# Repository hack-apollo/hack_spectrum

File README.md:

Hack Labs Audio Spectrum ：https://www.youtube.com/watch?v=lrZFiLHbFRo&lc=Ugw5ZR2V5kvy2mBF6H14AaABAg                                                                                
Author: HACK实验室                                                                                     
YouTube ID: HACK实验室, welcome to subscribe https://www.youtube.com/channel/UCxFY1FcIYK9d7riTvIh6eiA                                                         
Hack Audio Spectrum is a free download and may be used, modified, evaluated and
distributed without charge provided the user adheres to version three of the GNU
General Public License (GPL) and does not remove the copyright notice or this
text.  The GPL V3 text is available on the gnu.org web site
作者：HACK实验室                                                                                        
B站ID：HACK实验室  欢迎订阅 https://space.bilibili.com/395145107                                                                            
微信公众号：HACK实验室，开源资料唯一发布点，定期分享开源硬件以及有价值的技术文章，欢迎关注.

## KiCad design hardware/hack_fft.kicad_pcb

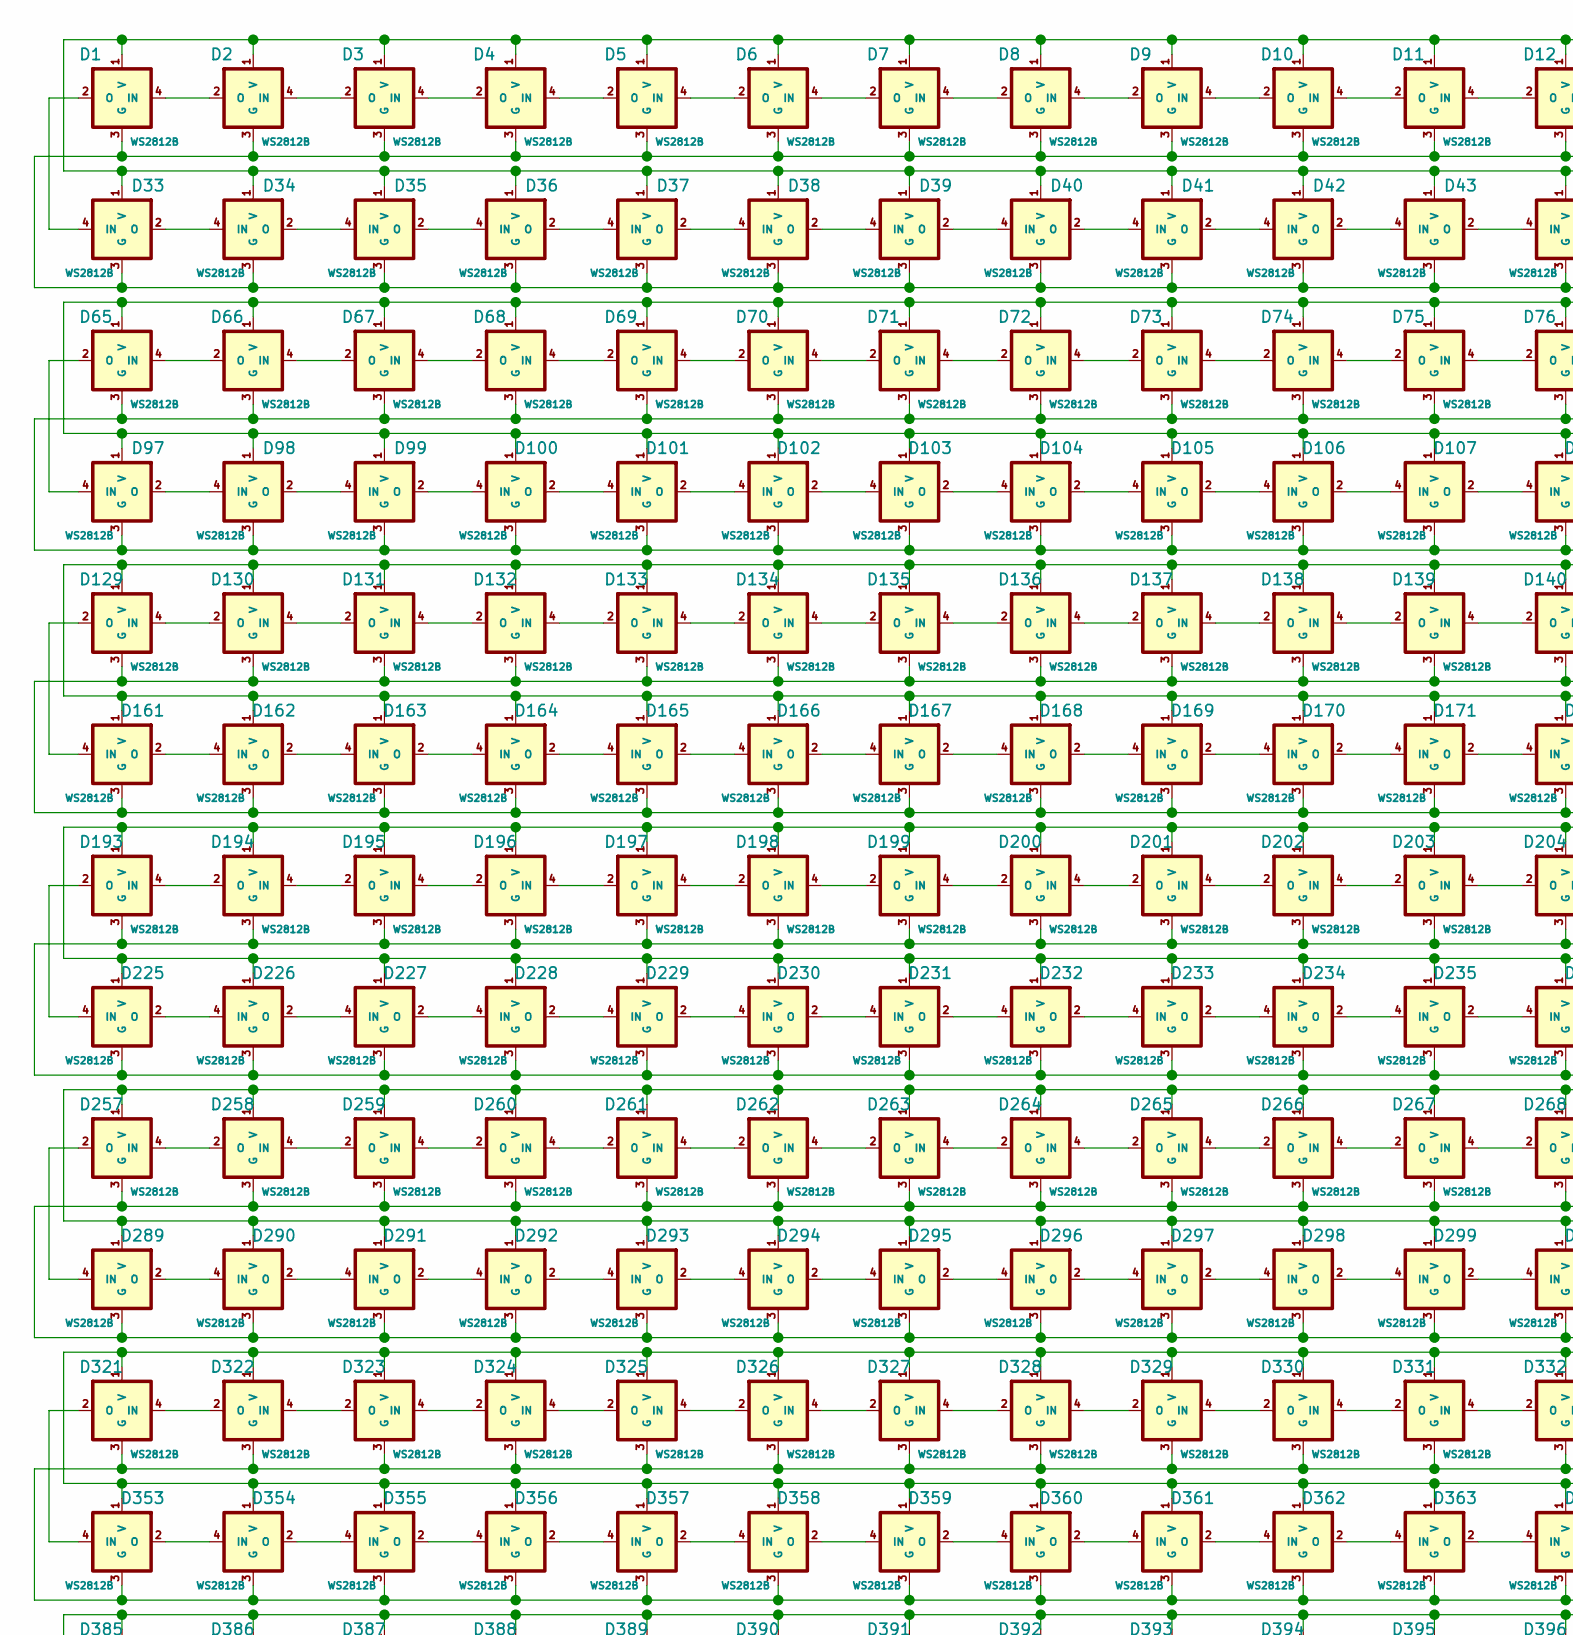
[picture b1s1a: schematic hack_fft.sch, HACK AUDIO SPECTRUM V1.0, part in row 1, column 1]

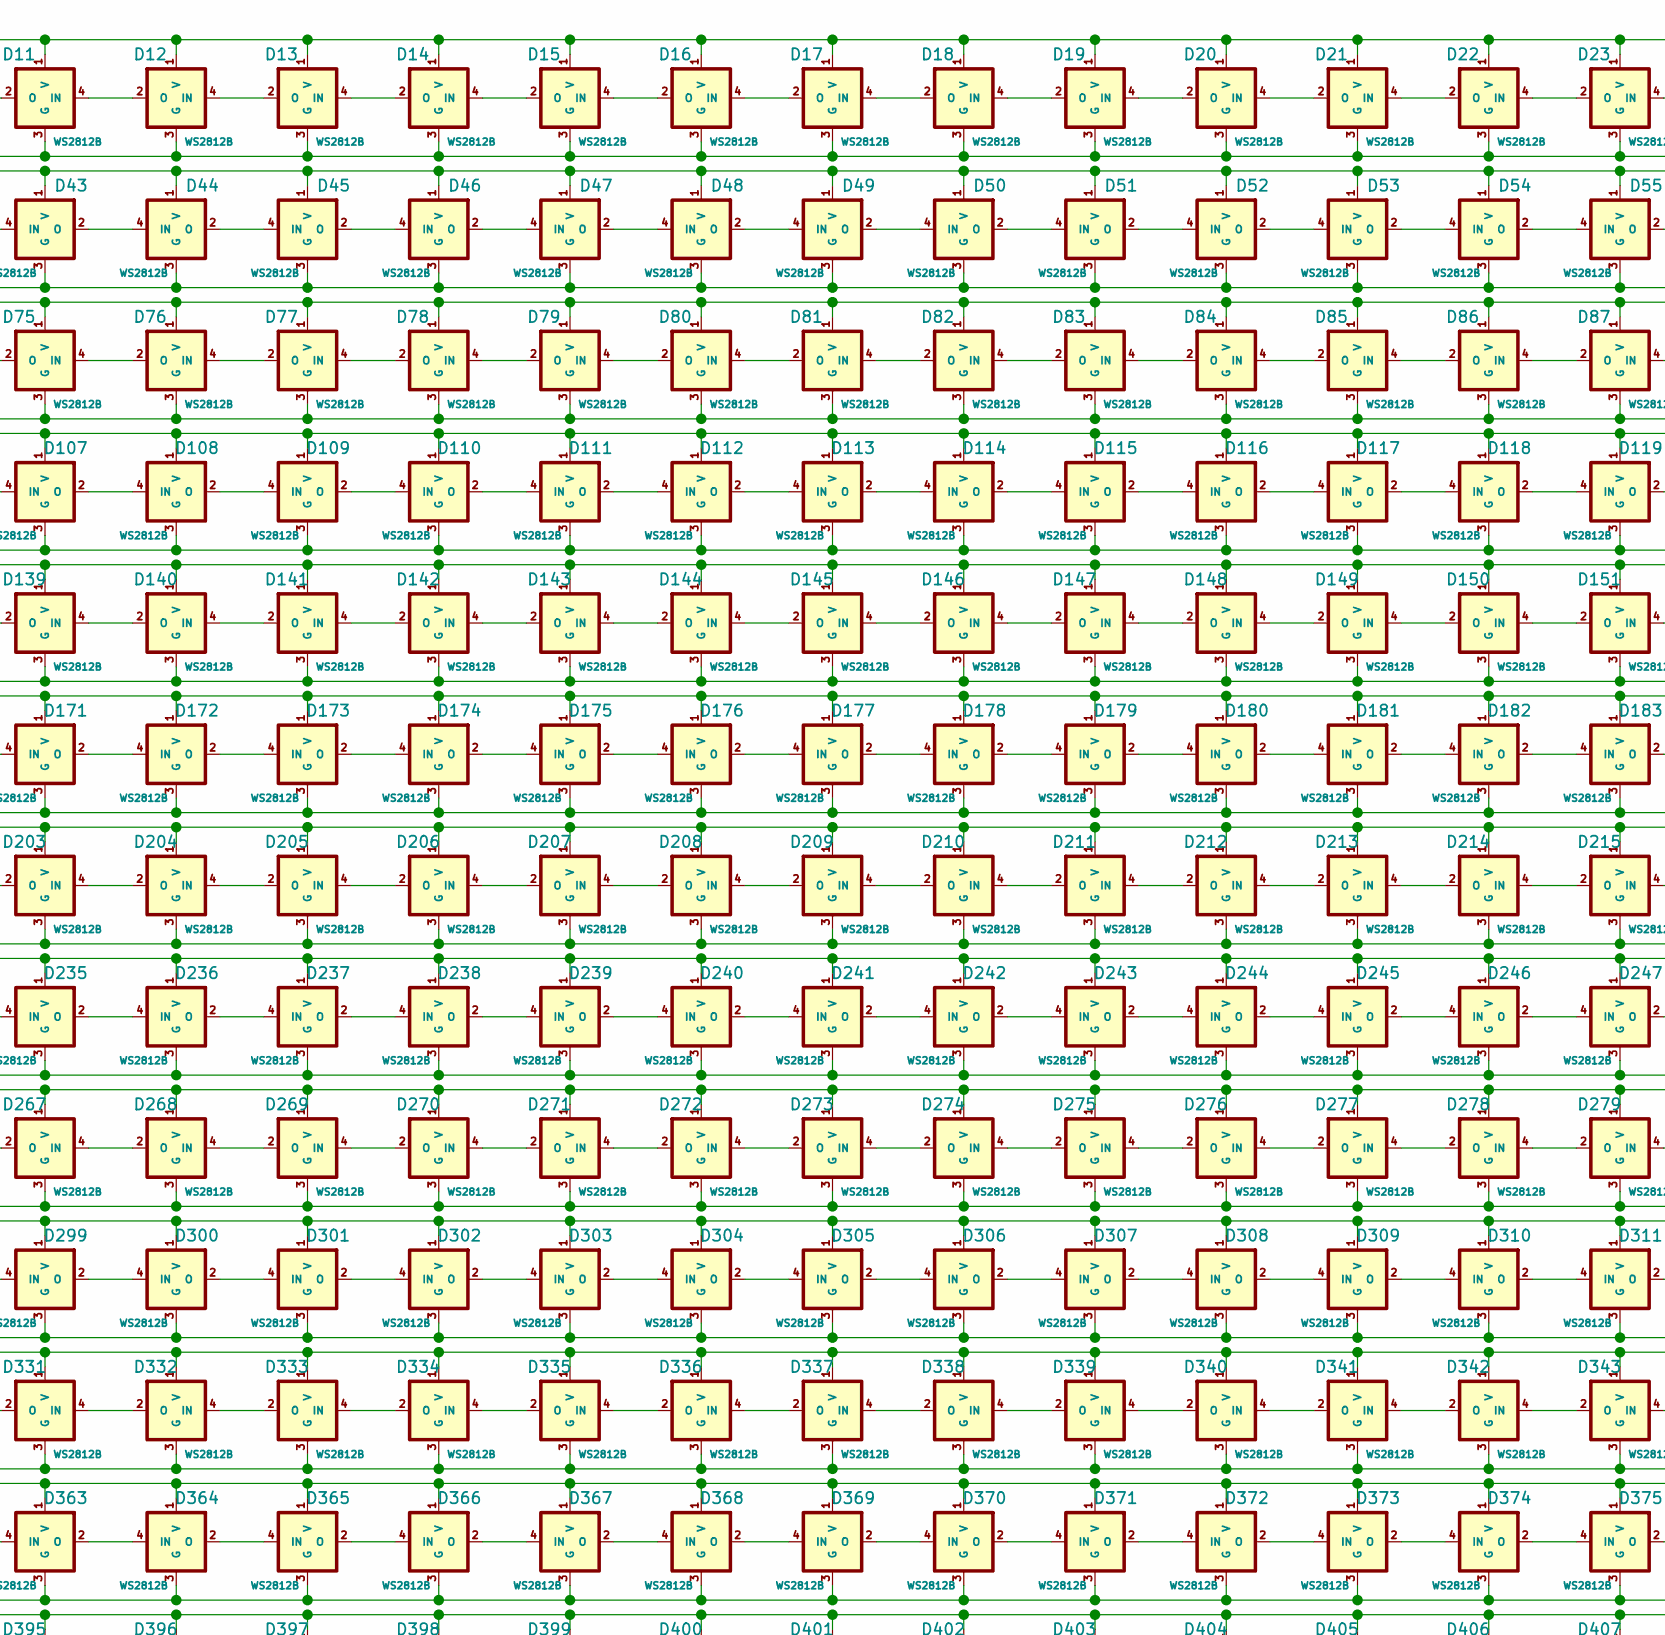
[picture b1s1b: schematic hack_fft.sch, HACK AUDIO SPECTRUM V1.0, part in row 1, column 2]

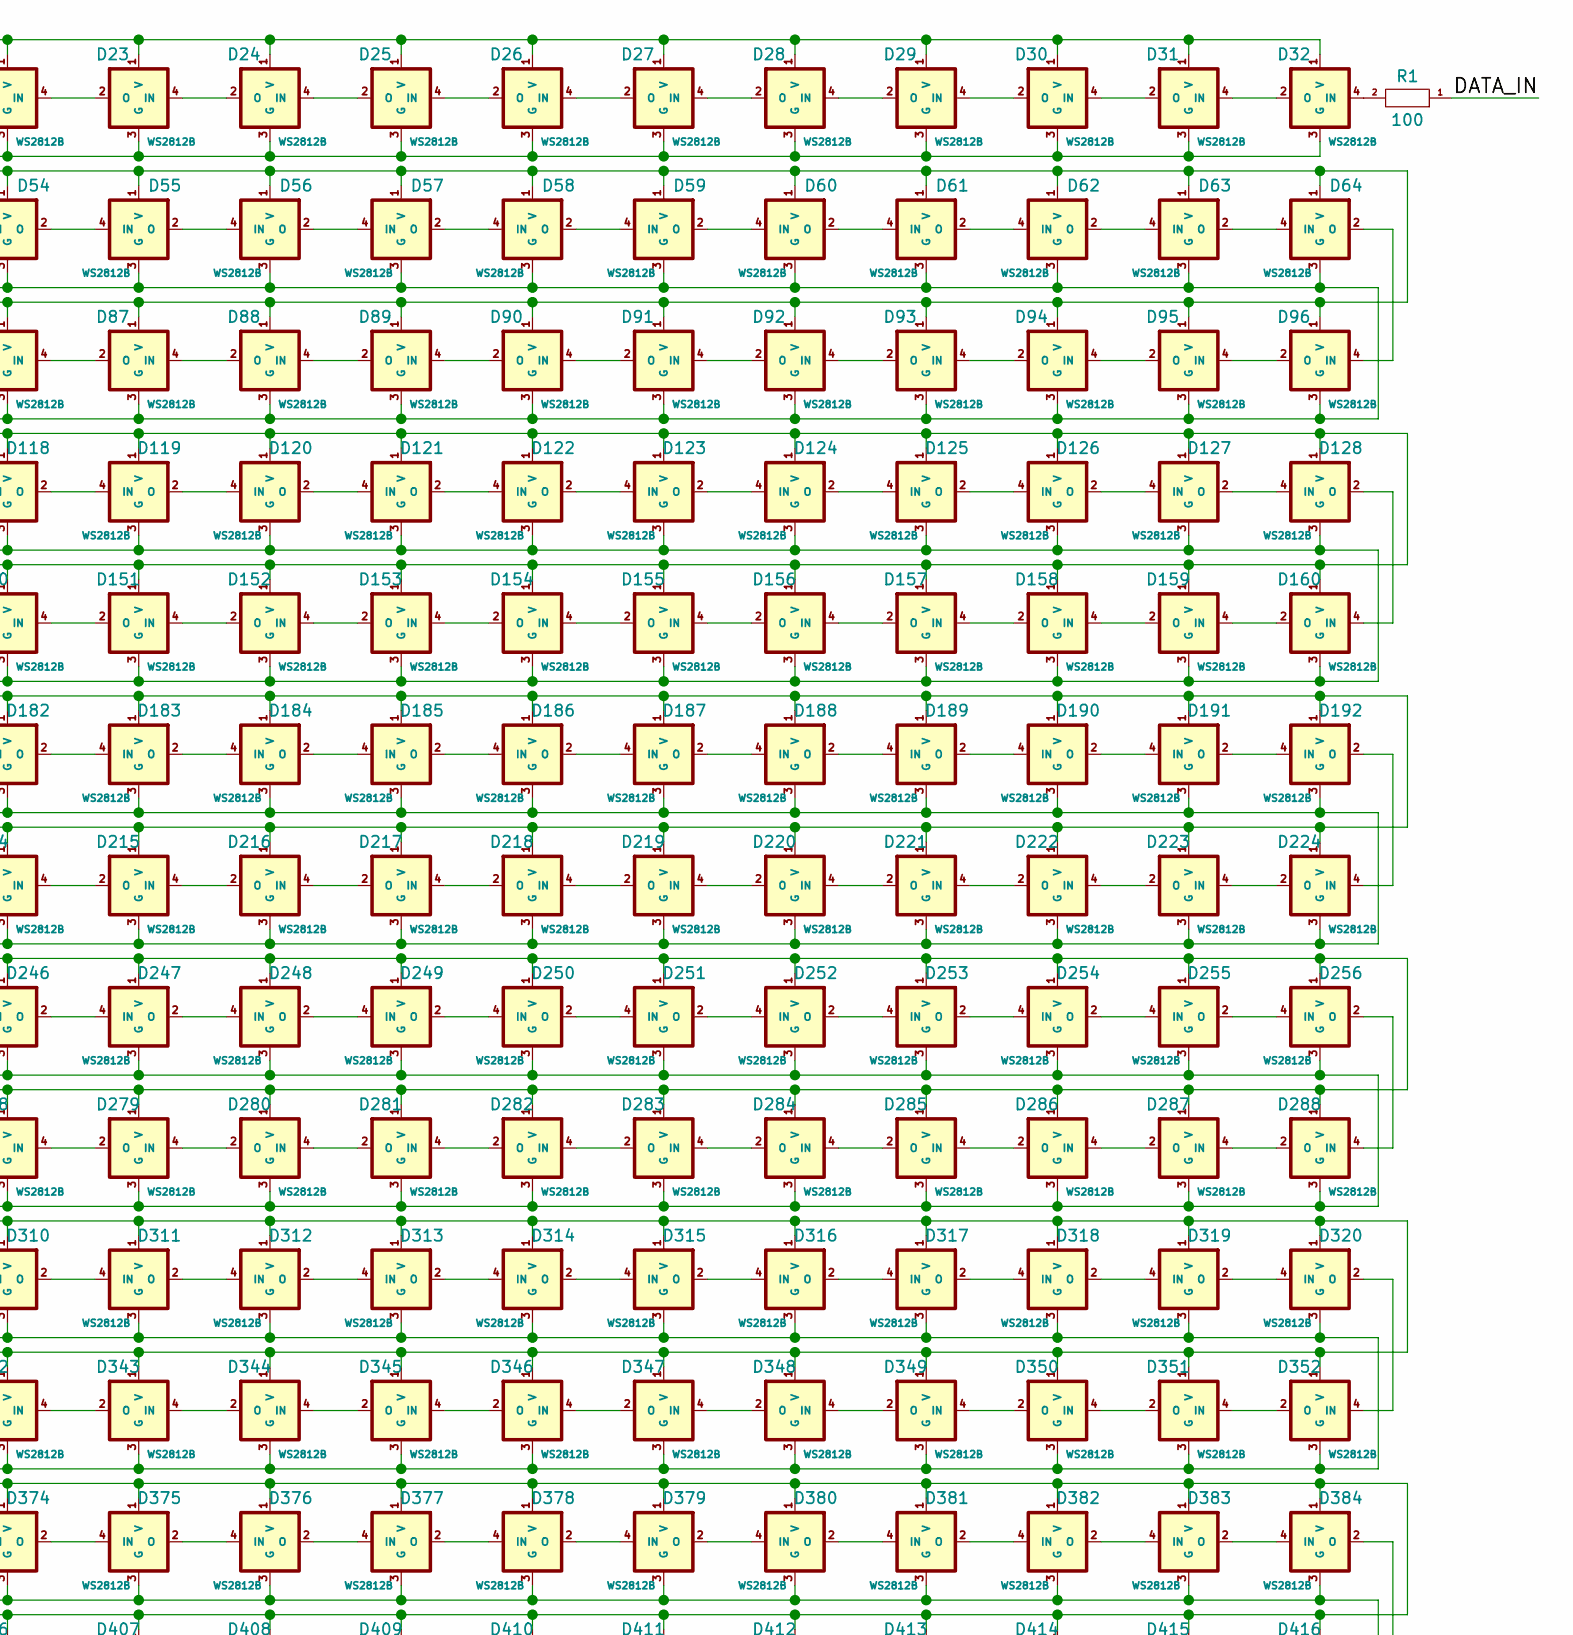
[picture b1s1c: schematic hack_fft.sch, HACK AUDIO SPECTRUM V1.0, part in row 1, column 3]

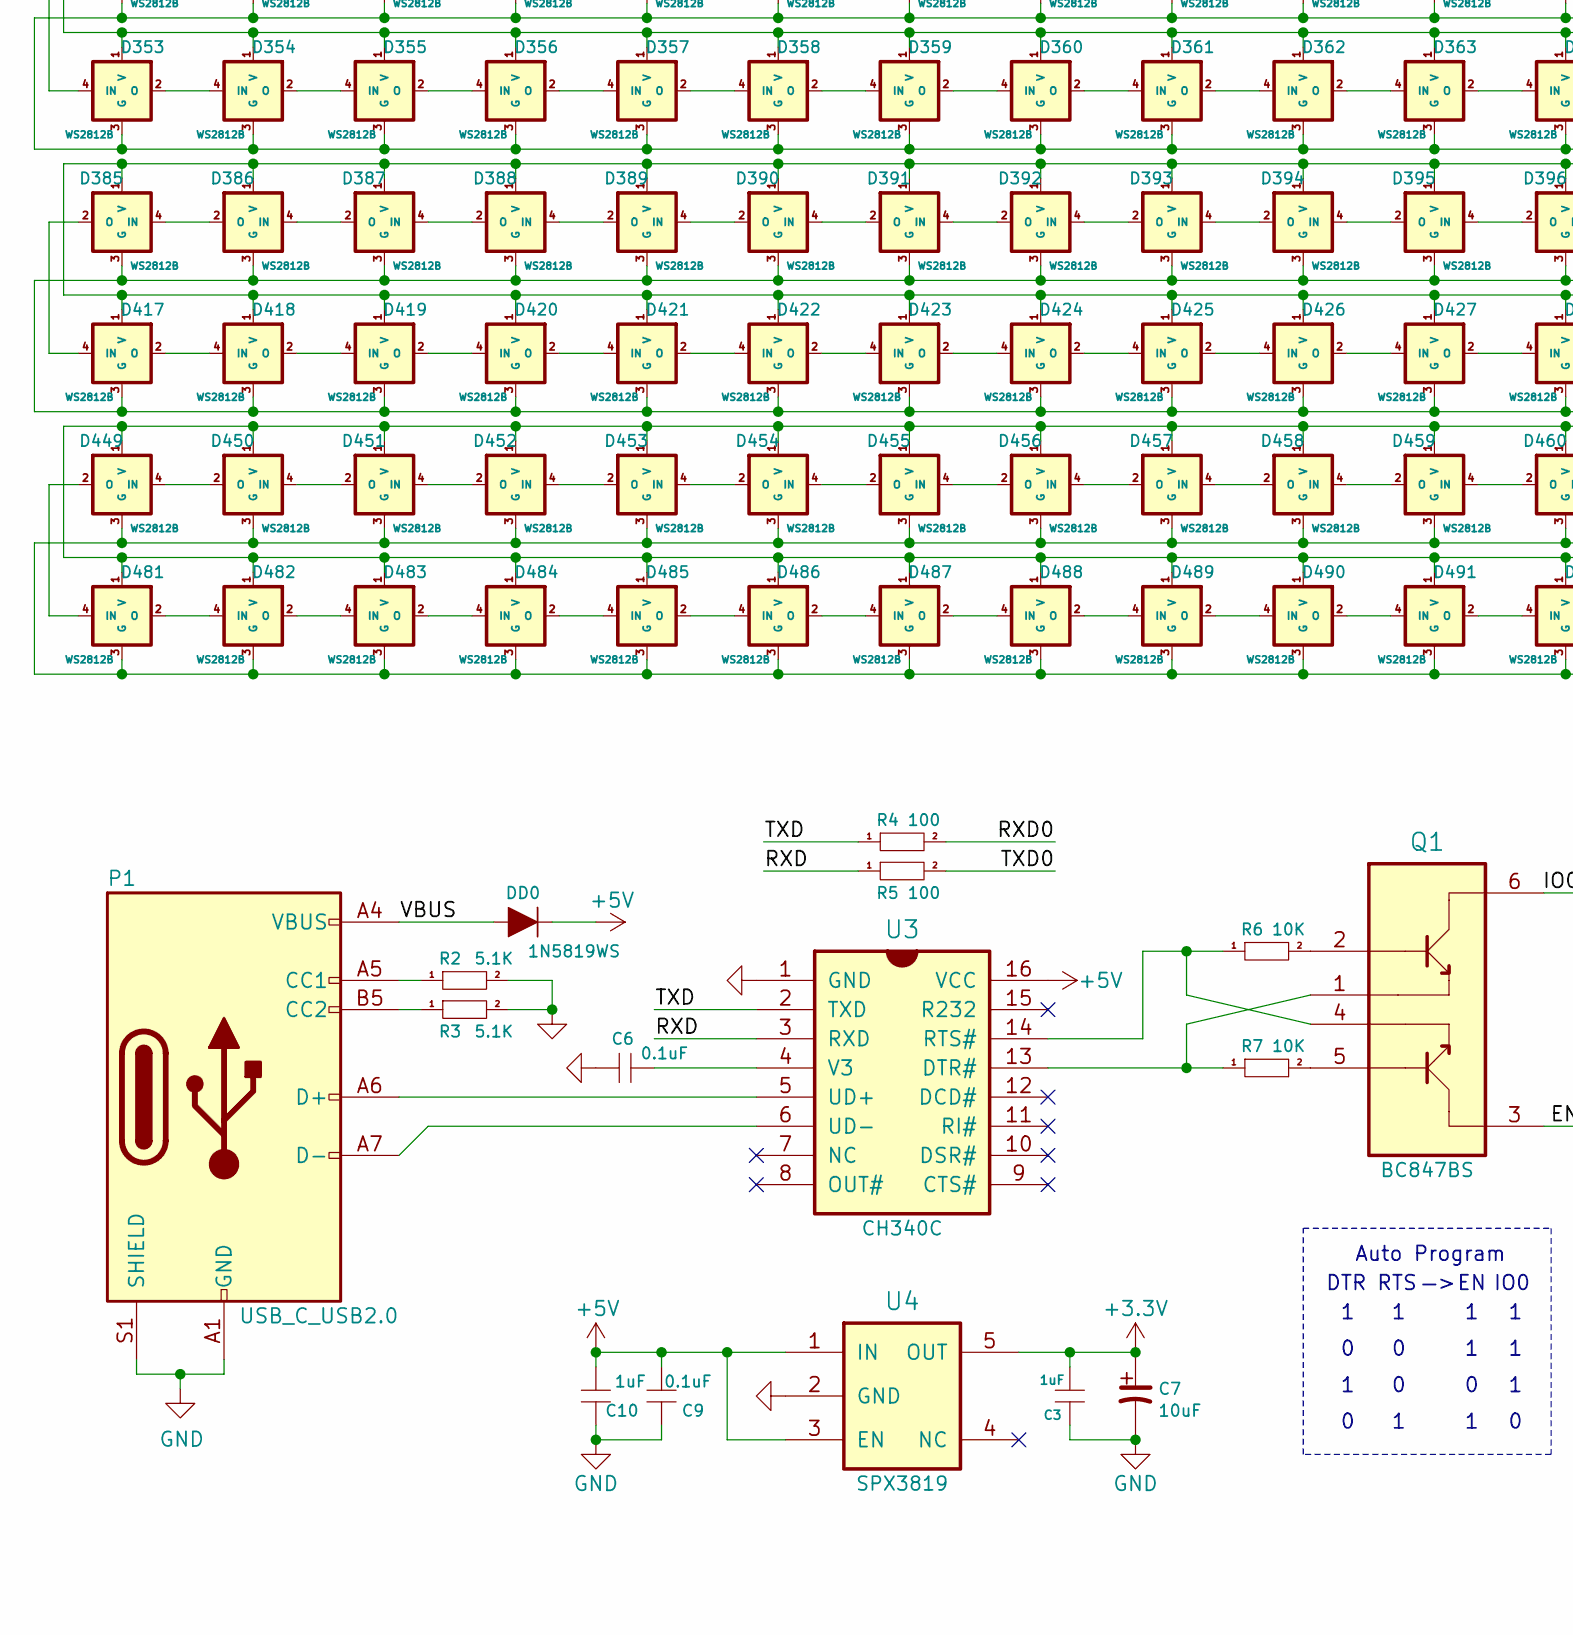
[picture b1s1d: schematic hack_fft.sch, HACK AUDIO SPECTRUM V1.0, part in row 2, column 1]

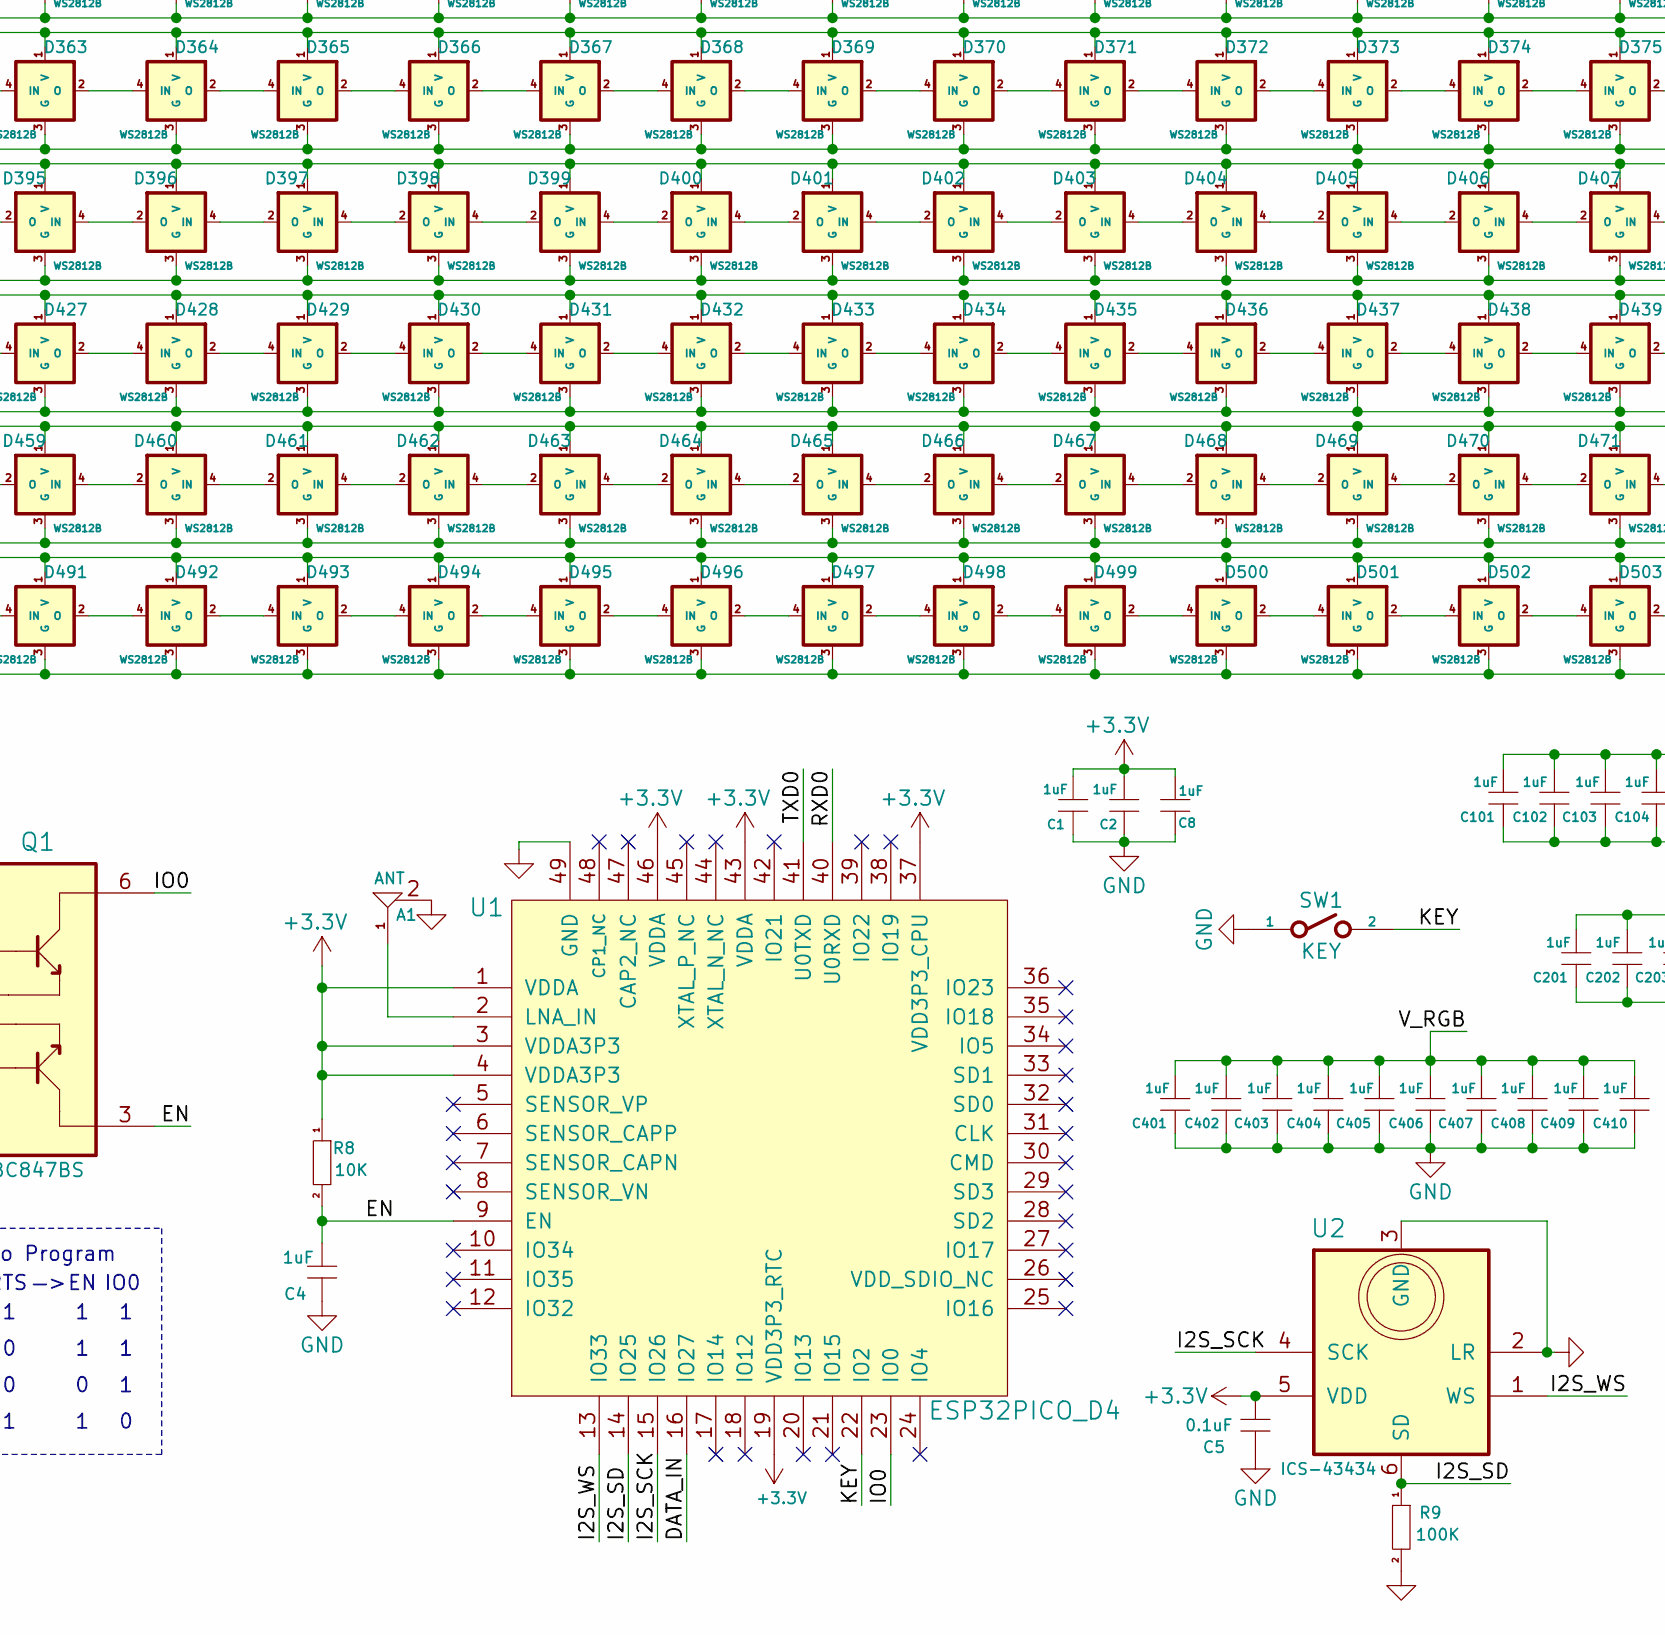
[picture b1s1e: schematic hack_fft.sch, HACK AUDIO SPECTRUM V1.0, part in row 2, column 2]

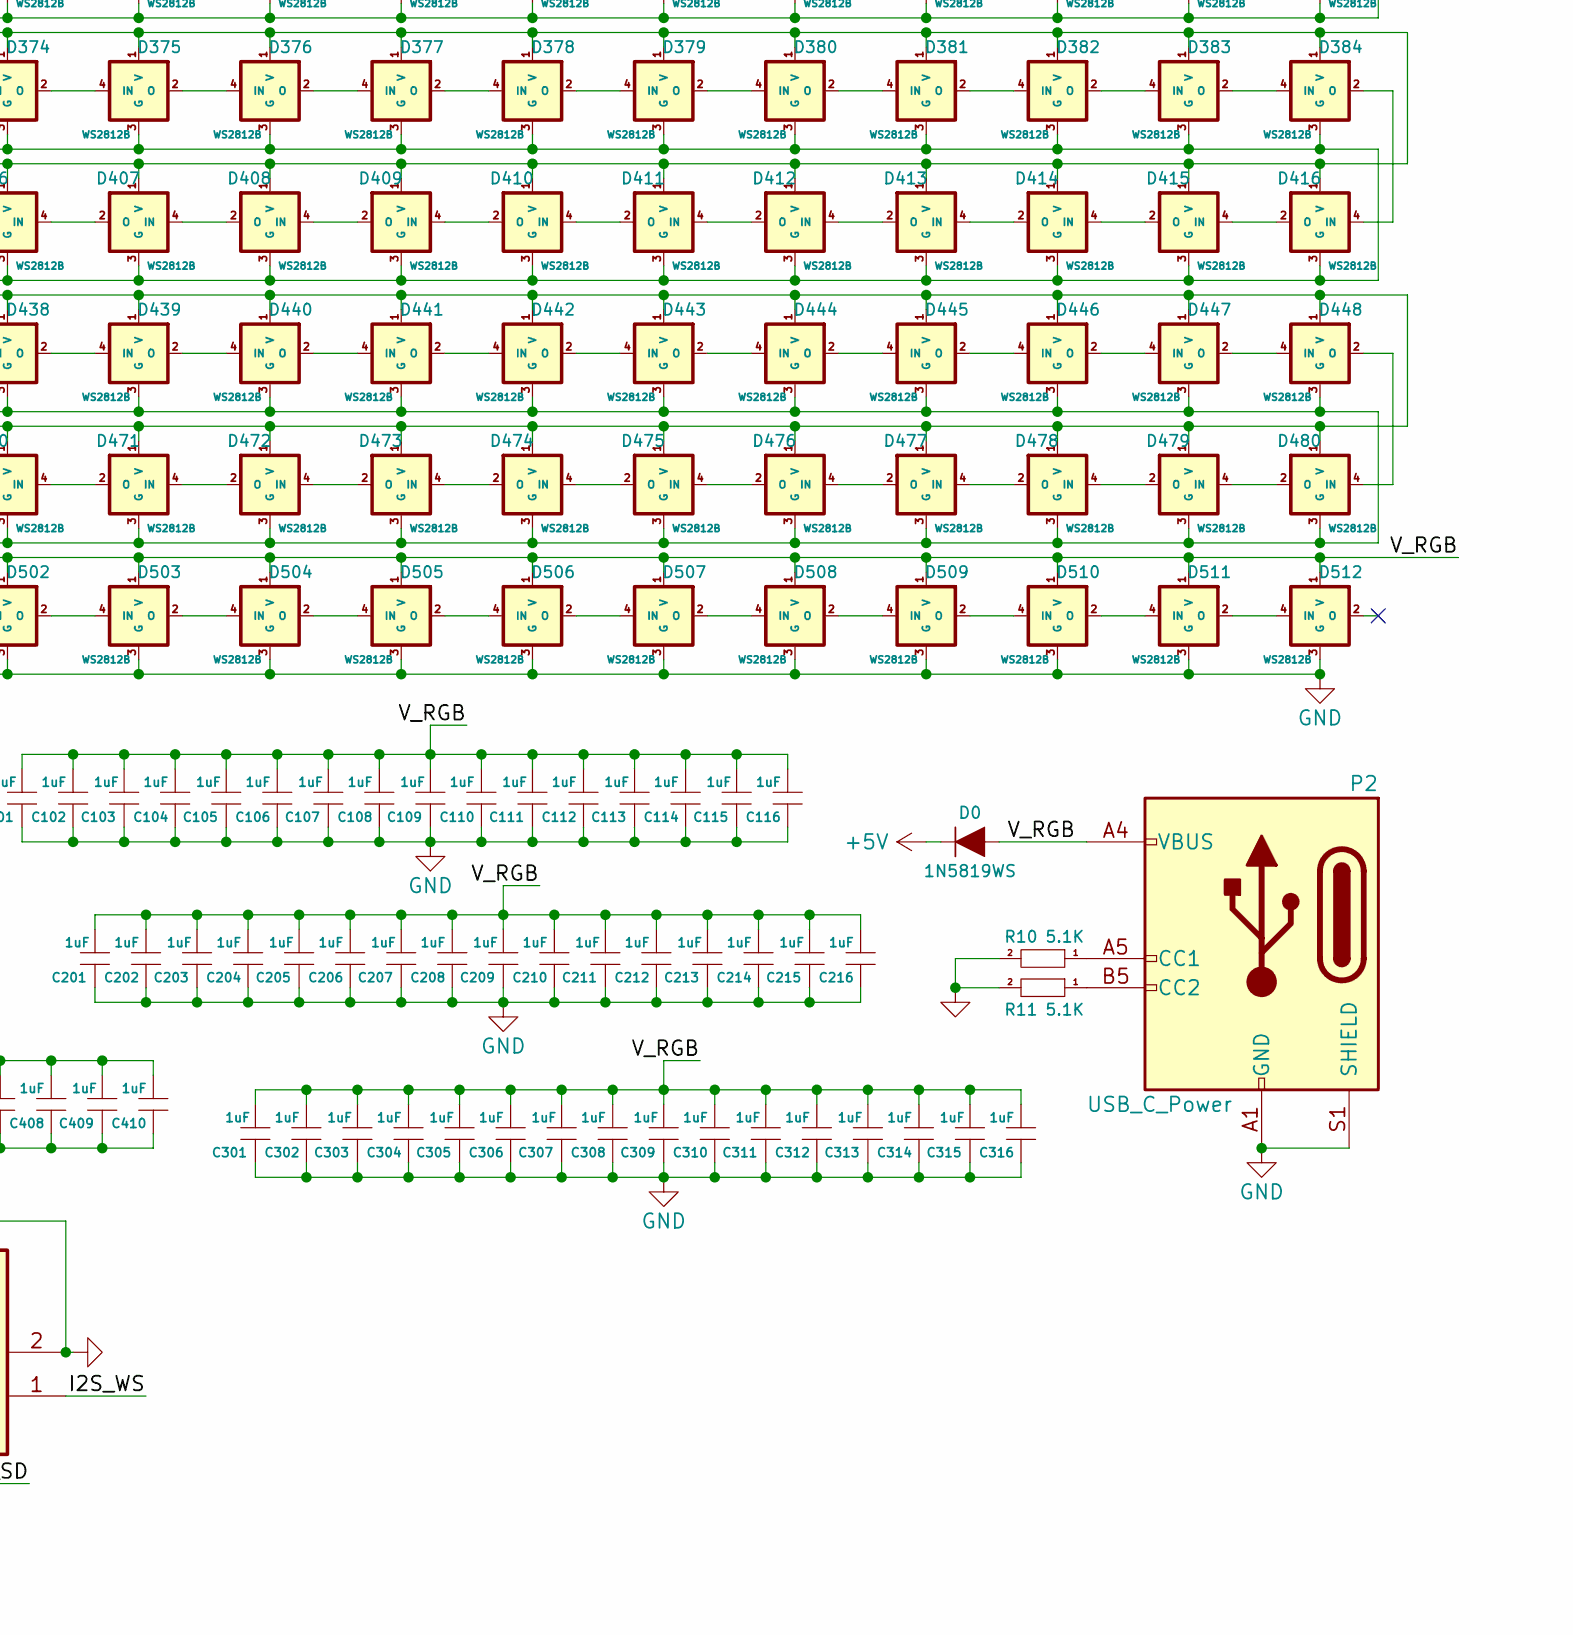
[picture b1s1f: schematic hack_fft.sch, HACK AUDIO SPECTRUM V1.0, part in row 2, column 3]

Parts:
A1: ANT; ProAnt_PRO-OB-440
C1, C2, C3, C4, C8, C10, C101, C102, C103, C104, C105, C106, C107, C108, C109, C110, C111, C112, C113, C114, C115, C116, C201, C202, C203, C204, C205, C206, C207, C208, C209, C210, C211, C212, C213, C214, C215, C216, C301, C302, C303, C304, C305, C306, C307, C308, C309, C310, C311, C312, C313, C314, C315, C316, C401, C402, C403, C404, C405, C406, C407, C408, C409, C410: 1uF; 0603_C
C5, C6, C9: 0.1uF; 0603_C
C7: 10uF; TantalC_SizeT_3528
D0: 1N5819WS; F_1206
D1, D2, D3, D4, D5, D6, D7, D8, D9, D10, D11, D12, D13, D14, D15, D16, D17, D18, D19, D20, D21, D22, D23, D24, D25, D26, D27, D28, D29, D30, D31, D32, D33, D34, D35, D36, D37, D38, D39, D40, D41, D42, D43, D44, D45, D46, D47, D48, D49, D50, D51, D52, D53, D54, D55, D56, D57, D58, D59, D60, D61, D62, D63, D64, D65, D66, D67, D68, D69, D70, D71, D72, D73, D74, D75, D76, D77, D78, D79, D80, D81, D82, D83, D84, D85, D86, D87, D88, D89, D90, D91, D92, D93, D94, D95, D96, D97, D98, D99, D100, D101, D102, D103, D104, D105, D106, D107, D108, D109, D110, D111, D112, D113, D114, D115, D116, D117, D118, D119, D120, D121, D122, D123, D124, D125, D126, D127, D128, D129, D130, D131, D132, D133, D134, D135, D136, D137, D138, D139, D140, D141, D142, D143, D144, D145, D146, D147, D148, D149, D150, D151, D152, D153, D154, D155, D156, D157, D158, D159, D160, D161, D162, D163, D164, D165, D166, D167, D168, D169, D170, D171, D172, D173, D174, D175, D176, D177, D178, D179, D180, D181, D182, D183, D184, D185, D186, D187, D188, D189, D190, D191, D192, D193, D194, D195, D196, D197, D198, D199, D200, D201, D202, D203, D204, D205, D206, D207, D208, D209, D210, D211, D212, D213, D214, D215, D216, D217, D218, D219, D220, D221, D222, D223, D224, D225, D226, D227, D228, D229, D230, D231, D232, D233, D234, D235, D236, D237, D238, D239, D240, D241, D242, D243, D244, D245, D246, D247, D248, D249, D250, D251, D252, D253, D254, D255, D256, D257, D258, D259, D260, D261, D262, D263, D264, D265, D266, D267, D268, D269, D270, D271, D272, D273, D274, D275, D276, D277, D278, D279, D280, D281, D282, D283, D284, D285, D286, D287, D288, D289, D290, D291, D292, D293, D294, D295, D296, D297, D298, D299, D300, D301, D302, D303, D304, D305, D306, D307, D308, D309, D310, D311, D312, D313, D314, D315, D316, D317, D318, D319, D320, D321, D322, D323, D324, D325, D326, D327, D328, D329, D330, D331, D332, D333, D334, D335, D336, D337, D338, D339, D340, D341, D342, D343, D344, D345, D346, D347, D348, D349, D350, D351, D352, D353, D354, D355, D356, D357, D358, D359, D360, D361, D362, D363, D364, D365, D366, D367, D368, D369, D370, D371, D372, D373, D374, D375, D376, D377, D378, D379, D380, D381, D382, D383, D384, D385, D386, D387, D388, D389, D390, D391, D392, D393, D394, D395, D396, D397, D398, D399, D400, D401, D402, D403, D404, D405, D406, D407, D408, D409, D410, D411, D412, D413, D414, D415, D416, D417, D418, D419, D420, D421, D422, D423, D424, D425, D426, D427, D428, D429, D430, D431, D432, D433, D434, D435, D436, D437, D438, D439, D440, D441, D442, D443, D444, D445, D446, D447, D448, D449, D450, D451, D452, D453, D454, D455, D456, D457, D458, D459, D460, D461, D462, D463, D464, D465, D466, D467, D468, D469, D470, D471, D472, D473, D474, D475, D476, D477, D478, D479, D480, D481, D482, D483, D484, D485, D486, D487, D488, D489, D490, D491, D492, D493, D494, D495, D496, D497, D498, D499, D500, D501, D502, D503, D504, D505, D506, D507, D508, D509, D510, D511, D512: WS2812B; LED_WS2812B_3.5x3.5mm
DD0: 1N5819WS; F_1206
P1: USB_C_USB2.0; USB-Type-C-SMD
P2: USB_C_Power; USB-Type-C-Stand
Q1: BC847BS; SOT363
R1, R4, R5: 100; 0603_R
R2, R3, R10, R11: 5.1K; 0603_R
R6, R7, R8: 10K; 0603_R
R9: 100K; 0603_R
SW1: KEY; SWITCH_PUSH_4
U1: ESP32PICO_D4; QFN-48-1EP_7x7mm_P0.5mm_ESP32PICO-D4
U2: ICS-43434
U3: CH340C; SOP-16
U4: SPX3819; SOT23-5

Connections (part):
+3V3: C1.2, C2.2, C3.2, C5.2, C7.1, C8.2, R8.1, U1.1 (VDDA), U1.3 (VDDA3P3), U1.4 (VDDA3P3), U1.19 (VDD3P3_RTC), U1.37 (VDD3P3_CPU), U1.43 (VDDA), U1.46 (VDDA), U2.5 (VDD), U4.5 (OUT)
+5V: C9.2, C10.2, D0.2 (K), DD0.2 (K), U3.16 (VCC), U4.1 (IN), U4.3 (EN)
/DATA_IN: R1.1, U1.16 (IO27)
/EN: C4.2, Q1.3, R8.2, U1.9 (EN)
/I2S_SCK: U1.15 (IO26), U2.4 (SCK)
/I2S_SD: R9.1, U1.14 (IO25), U2.6 (SD)
/I2S_WS: U1.13 (IO33), U2.1 (WS)
/IO0: Q1.6, U1.23 (IO0)
/KEY: SW1.2, U1.22 (IO2)
/RXD: R5.1, U3.3 (RXD)
/RXD0: R4.2, U1.40 (U0RXD)
/TXD: R4.1, U3.2 (TXD)
/TXD0: R5.2, U1.41 (U0TXD)
/VBUS: DD0.1 (A), P1.A4 (VBUS), P1.A9 (VBUS), P1.B4 (VBUS), P1.B9 (VBUS)
/V_RGB: C101.2, C102.2, C103.2, C104.2, C105.2, C106.2, C107.2, C108.2, C109.2, C110.2, C111.2, C112.2, C113.2, C114.2, C115.2, C116.2, C201.2, C202.2, C203.2, C204.2, C205.2, C206.2, C207.2, C208.2, C209.2, C210.2, C211.2, C212.2, C213.2, C214.2, C215.2, C216.2, C301.2, C302.2, C303.2, C304.2, C305.2, C306.2, C307.2, C308.2, C309.2, C310.2, C311.2, C312.2, C313.2, C314.2, C315.2, C316.2, C401.2, C402.2, C403.2, C404.2, C405.2, C406.2, C407.2, C408.2, C409.2, C410.2, D0.1 (A), D1.1 (V), D2.1 (V), D3.1 (V), D4.1 (V), D5.1 (V), D6.1 (V), D7.1 (V), D8.1 (V), D9.1 (V), D10.1 (V), D11.1 (V), D12.1 (V), D13.1 (V), D14.1 (V), D15.1 (V), D16.1 (V), D17.1 (V), D18.1 (V), D19.1 (V), D20.1 (V), D21.1 (V)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; also elsewhere on the board
GND: A1.2, C1.1, C2.1, C3.1, C4.1, C5.1, C6.1, C7.2, C8.1, C9.1, C10.1, C101.1, C102.1, C103.1, C104.1, C105.1, C106.1, C107.1, C108.1, C109.1, C110.1, C111.1, C112.1, C113.1, C114.1, C115.1, C116.1, C201.1, C202.1, C203.1, C204.1, C205.1, C206.1, C207.1, C208.1, C209.1, C210.1, C211.1, C212.1, C213.1, C214.1, C215.1, C216.1, C301.1, C302.1, C303.1, C304.1, C305.1, C306.1, C307.1, C308.1, C309.1, C310.1, C311.1, C312.1, C313.1, C314.1, C315.1, C316.1, C401.1, C402.1, C403.1, C404.1, C405.1, C406.1, C407.1, C408.1, C409.1, C410.1, D1.3 (G), D2.3 (G), D3.3 (G), D4.3 (G), D5.3 (G), D6.3 (G), D7.3 (G), D8.3 (G), D9.3 (G), D10.3 (G), D11.3 (G)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; also elsewhere on the board
unnamed: A1.1, U1.2 (LNA_IN)
unnamed: C6.2, U3.4 (V3)
unnamed: D1.2 (O), D33.4 (IN)
unnamed: D1.4 (IN), D2.2 (O)
unnamed: D2.4 (IN), D3.2 (O)
unnamed: D3.4 (IN), D4.2 (O)
unnamed: D4.4 (IN), D5.2 (O)
unnamed: D5.4 (IN), D6.2 (O)
unnamed: D6.4 (IN), D7.2 (O)
unnamed: D7.4 (IN), D8.2 (O)
unnamed: D8.4 (IN), D9.2 (O)
unnamed: D9.4 (IN), D10.2 (O)
unnamed: D10.4 (IN), D11.2 (O)
unnamed: D11.4 (IN), D12.2 (O)
unnamed: D12.4 (IN), D13.2 (O)
unnamed: D13.4 (IN), D14.2 (O)
unnamed: D14.4 (IN), D15.2 (O)
unnamed: D15.4 (IN), D16.2 (O)
unnamed: D16.4 (IN), D17.2 (O)
unnamed: D17.4 (IN), D18.2 (O)
unnamed: D18.4 (IN), D19.2 (O)
unnamed: D19.4 (IN), D20.2 (O)
unnamed: D20.4 (IN), D21.2 (O)
unnamed: D21.4 (IN), D22.2 (O)
unnamed: D22.4 (IN), D23.2 (O)
unnamed: D23.4 (IN), D24.2 (O)
unnamed: D24.4 (IN), D25.2 (O)
unnamed: D25.4 (IN), D26.2 (O)
unnamed: D26.4 (IN), D27.2 (O)
unnamed: D27.4 (IN), D28.2 (O)
unnamed: D28.4 (IN), D29.2 (O)
unnamed: D29.4 (IN), D30.2 (O)
unnamed: D30.4 (IN), D31.2 (O)
unnamed: D31.4 (IN), D32.2 (O)
unnamed: D32.4 (IN), R1.2
unnamed: D33.2 (O), D34.4 (IN)
unnamed: D34.2 (O), D35.4 (IN)
unnamed: D35.2 (O), D36.4 (IN)
unnamed: D36.2 (O), D37.4 (IN)
unnamed: D37.2 (O), D38.4 (IN)
unnamed: D38.2 (O), D39.4 (IN)
unnamed: D39.2 (O), D40.4 (IN)
unnamed 58: D40.2 (O), D41.4 (IN); also elsewhere on the board
unnamed 59: D41.2 (O), D42.4 (IN); also elsewhere on the board
unnamed: D42.2 (O), D43.4 (IN)
unnamed: D43.2 (O), D44.4 (IN)
unnamed: D44.2 (O), D45.4 (IN)
unnamed: D45.2 (O), D46.4 (IN)
unnamed: D46.2 (O), D47.4 (IN)
unnamed: D47.2 (O), D48.4 (IN)
unnamed: D48.2 (O), D49.4 (IN)
unnamed: D49.2 (O), D50.4 (IN)
unnamed: D50.2 (O), D51.4 (IN)
unnamed: D51.2 (O), D52.4 (IN)
unnamed: D52.2 (O), D53.4 (IN)
unnamed: D53.2 (O), D54.4 (IN)
unnamed: D54.2 (O), D55.4 (IN)
unnamed: D55.2 (O), D56.4 (IN)
unnamed: D56.2 (O), D57.4 (IN)
unnamed: D57.2 (O), D58.4 (IN)
unnamed: D58.2 (O), D59.4 (IN)
unnamed: D59.2 (O), D60.4 (IN)
unnamed: D60.2 (O), D61.4 (IN)
unnamed: D61.2 (O), D62.4 (IN)
unnamed: D62.2 (O), D63.4 (IN)
unnamed: D63.2 (O), D64.4 (IN)
unnamed: D64.2 (O), D96.4 (IN)
unnamed: D65.2 (O), D97.4 (IN)
unnamed: D65.4 (IN), D66.2 (O)
unnamed: D66.4 (IN), D67.2 (O)
unnamed: D67.4 (IN), D68.2 (O)
unnamed: D68.4 (IN), D69.2 (O)
unnamed: D69.4 (IN), D70.2 (O)
unnamed: D70.4 (IN), D71.2 (O)
unnamed: D71.4 (IN), D72.2 (O)
unnamed: D72.4 (IN), D73.2 (O)
unnamed: D73.4 (IN), D74.2 (O)
unnamed: D74.4 (IN), D75.2 (O)
unnamed: D75.4 (IN), D76.2 (O)
unnamed: D76.4 (IN), D77.2 (O)
unnamed: D77.4 (IN), D78.2 (O)
unnamed: D78.4 (IN), D79.2 (O)
unnamed: D79.4 (IN), D80.2 (O)
unnamed: D80.4 (IN), D81.2 (O)
unnamed: D81.4 (IN), D82.2 (O)
unnamed: D82.4 (IN), D83.2 (O)
unnamed: D83.4 (IN), D84.2 (O)
unnamed: D84.4 (IN), D85.2 (O)
unnamed: D85.4 (IN), D86.2 (O)
unnamed: D86.4 (IN), D87.2 (O)
unnamed: D87.4 (IN), D88.2 (O)
unnamed: D88.4 (IN), D89.2 (O)
unnamed: D89.4 (IN), D90.2 (O)
unnamed: D90.4 (IN), D91.2 (O)
unnamed: D91.4 (IN), D92.2 (O)
unnamed: D92.4 (IN), D93.2 (O)
unnamed: D93.4 (IN), D94.2 (O)
unnamed: D94.4 (IN), D95.2 (O)
unnamed: D95.4 (IN), D96.2 (O)
unnamed: D97.2 (O), D98.4 (IN)
unnamed: D98.2 (O), D99.4 (IN)
unnamed: D100.2 (O), D101.4 (IN)
unnamed: D99.2 (O), D100.4 (IN)
unnamed: D101.2 (O), D102.4 (IN)
unnamed: D102.2 (O), D103.4 (IN)
unnamed: D103.2 (O), D104.4 (IN)
unnamed: D104.2 (O), D105.4 (IN)
unnamed: D105.2 (O), D106.4 (IN)
unnamed: D106.2 (O), D107.4 (IN)
unnamed: D107.2 (O), D108.4 (IN)
unnamed: D108.2 (O), D109.4 (IN)
unnamed: D109.2 (O), D110.4 (IN)
unnamed: D110.2 (O), D111.4 (IN)
unnamed: D111.2 (O), D112.4 (IN)
unnamed: D112.2 (O), D113.4 (IN)
unnamed: D113.2 (O), D114.4 (IN)
unnamed: D114.2 (O), D115.4 (IN)
unnamed: D115.2 (O), D116.4 (IN)
unnamed: D116.2 (O), D117.4 (IN)
unnamed: D117.2 (O), D118.4 (IN)
unnamed: D118.2 (O), D119.4 (IN)
unnamed: D119.2 (O), D120.4 (IN)
unnamed: D120.2 (O), D121.4 (IN)
unnamed: D121.2 (O), D122.4 (IN)
unnamed: D122.2 (O), D123.4 (IN)
unnamed: D123.2 (O), D124.4 (IN)
unnamed: D124.2 (O), D125.4 (IN)
unnamed: D125.2 (O), D126.4 (IN)
unnamed: D126.2 (O), D127.4 (IN)
unnamed: D127.2 (O), D128.4 (IN)
unnamed: D128.2 (O), D160.4 (IN)
unnamed: D129.2 (O), D161.4 (IN)
unnamed: D129.4 (IN), D130.2 (O)
unnamed: D130.4 (IN), D131.2 (O)
unnamed: D131.4 (IN), D132.2 (O)
unnamed: D132.4 (IN), D133.2 (O)
unnamed: D133.4 (IN), D134.2 (O)
unnamed: D134.4 (IN), D135.2 (O)
unnamed: D135.4 (IN), D136.2 (O)
unnamed: D136.4 (IN), D137.2 (O)
unnamed: D137.4 (IN), D138.2 (O)
unnamed: D138.4 (IN), D139.2 (O)
unnamed: D139.4 (IN), D140.2 (O)
unnamed: D140.4 (IN), D141.2 (O)
unnamed: D141.4 (IN), D142.2 (O)
unnamed: D142.4 (IN), D143.2 (O)
unnamed: D143.4 (IN), D144.2 (O)
unnamed: D144.4 (IN), D145.2 (O)
unnamed: D145.4 (IN), D146.2 (O)
unnamed: D146.4 (IN), D147.2 (O)
unnamed: D147.4 (IN), D148.2 (O)
unnamed: D148.4 (IN), D149.2 (O)
unnamed: D149.4 (IN), D150.2 (O)
unnamed: D150.4 (IN), D151.2 (O)
unnamed: D151.4 (IN), D152.2 (O)
unnamed: D152.4 (IN), D153.2 (O)
unnamed: D153.4 (IN), D154.2 (O)
unnamed: D154.4 (IN), D155.2 (O)
unnamed: D155.4 (IN), D156.2 (O)
unnamed: D156.4 (IN), D157.2 (O)
unnamed: D157.4 (IN), D158.2 (O)
unnamed: D158.4 (IN), D159.2 (O)
unnamed: D159.4 (IN), D160.2 (O)
unnamed: D161.2 (O), D162.4 (IN)
unnamed: D162.2 (O), D163.4 (IN)
unnamed: D163.2 (O), D164.4 (IN)
unnamed: D164.2 (O), D165.4 (IN)
unnamed: D165.2 (O), D166.4 (IN)
unnamed: D166.2 (O), D167.4 (IN)
unnamed: D167.2 (O), D168.4 (IN)
unnamed: D168.2 (O), D169.4 (IN)
unnamed: D169.2 (O), D170.4 (IN)
unnamed: D170.2 (O), D171.4 (IN)
unnamed: D171.2 (O), D172.4 (IN)
unnamed: D172.2 (O), D173.4 (IN)
unnamed: D173.2 (O), D174.4 (IN)
unnamed: D174.2 (O), D175.4 (IN)
unnamed: D175.2 (O), D176.4 (IN)
unnamed: D176.2 (O), D177.4 (IN)
unnamed: D177.2 (O), D178.4 (IN)
unnamed: D178.2 (O), D179.4 (IN)
unnamed: D179.2 (O), D180.4 (IN)
unnamed: D180.2 (O), D181.4 (IN)
unnamed: D181.2 (O), D182.4 (IN)
unnamed: D182.2 (O), D183.4 (IN)
unnamed: D183.2 (O), D184.4 (IN)
unnamed: D184.2 (O), D185.4 (IN)
unnamed: D185.2 (O), D186.4 (IN)
unnamed: D186.2 (O), D187.4 (IN)
unnamed: D187.2 (O), D188.4 (IN)
unnamed: D188.2 (O), D189.4 (IN)
unnamed: D189.2 (O), D190.4 (IN)
unnamed: D190.2 (O), D191.4 (IN)
unnamed: D191.2 (O), D192.4 (IN)
unnamed: D192.2 (O), D224.4 (IN)
unnamed: D193.2 (O), D225.4 (IN)
unnamed: D193.4 (IN), D194.2 (O)
unnamed: D194.4 (IN), D195.2 (O)
unnamed: D195.4 (IN), D196.2 (O)
unnamed: D196.4 (IN), D197.2 (O)
unnamed: D197.4 (IN), D198.2 (O)
unnamed: D198.4 (IN), D199.2 (O)
unnamed: D199.4 (IN), D200.2 (O)
unnamed: D200.4 (IN), D201.2 (O)
unnamed: D201.4 (IN), D202.2 (O)
unnamed: D202.4 (IN), D203.2 (O)
unnamed: D203.4 (IN), D204.2 (O)
unnamed: D204.4 (IN), D205.2 (O)
unnamed: D205.4 (IN), D206.2 (O)
unnamed: D206.4 (IN), D207.2 (O)
unnamed: D207.4 (IN), D208.2 (O)
unnamed: D208.4 (IN), D209.2 (O)
unnamed: D209.4 (IN), D210.2 (O)
unnamed: D210.4 (IN), D211.2 (O)
unnamed: D211.4 (IN), D212.2 (O)
unnamed: D212.4 (IN), D213.2 (O)
unnamed: D213.4 (IN), D214.2 (O)
unnamed: D214.4 (IN), D215.2 (O)
unnamed: D215.4 (IN), D216.2 (O)
unnamed: D216.4 (IN), D217.2 (O)
unnamed: D217.4 (IN), D218.2 (O)
unnamed: D218.4 (IN), D219.2 (O)
unnamed: D219.4 (IN), D220.2 (O)
unnamed: D220.4 (IN), D221.2 (O)
unnamed: D221.4 (IN), D222.2 (O)
unnamed: D222.4 (IN), D223.2 (O)
unnamed: D223.4 (IN), D224.2 (O)
unnamed: D225.2 (O), D226.4 (IN)
unnamed: D226.2 (O), D227.4 (IN)
unnamed: D227.2 (O), D228.4 (IN)
unnamed: D228.2 (O), D229.4 (IN)
unnamed: D229.2 (O), D230.4 (IN)
unnamed: D230.2 (O), D231.4 (IN)
unnamed: D231.2 (O), D232.4 (IN)
unnamed: D232.2 (O), D233.4 (IN)
unnamed: D233.2 (O), D234.4 (IN)
unnamed: D234.2 (O), D235.4 (IN)
unnamed: D235.2 (O), D236.4 (IN)
unnamed: D236.2 (O), D237.4 (IN)
unnamed: D237.2 (O), D238.4 (IN)
unnamed: D238.2 (O), D239.4 (IN)
unnamed: D239.2 (O), D240.4 (IN)
unnamed: D240.2 (O), D241.4 (IN)
unnamed: D241.2 (O), D242.4 (IN)
unnamed: D242.2 (O), D243.4 (IN)
unnamed: D243.2 (O), D244.4 (IN)
unnamed: D244.2 (O), D245.4 (IN)
unnamed: D245.2 (O), D246.4 (IN)
unnamed: D246.2 (O), D247.4 (IN)
unnamed: D247.2 (O), D248.4 (IN)
unnamed: D248.2 (O), D249.4 (IN)
unnamed: D249.2 (O), D250.4 (IN)
unnamed: D250.2 (O), D251.4 (IN)
unnamed: D251.2 (O), D252.4 (IN)
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
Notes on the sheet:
Auto Program
DTR
RTS
IO0
